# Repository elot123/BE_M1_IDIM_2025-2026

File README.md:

# BE_M1_IDIM_2025-2026

## Objectif du projet
Ce dépôt contient le travail réalisé dans le cadre du BE du M1 IDIM.
Il vise à modéliser et visualiser la trajectoire d’une particule à travers
différentes zones physiques.

## Description des fichiers

### `trajectoire.py`
Ce fichier contient les fonctions de calcul de la trajectoire :
- définition des paramètres géométriques des différentes zones
- calcul des positions et vitesses dans chaque zone
- fonction de tracé des trajectoires et des limites physiques

Il constitue le **cœur physique / mathématique** du projet.

### `interface_graphique.py`
Ce fichier implémente une interface graphique permettant :
- de modifier les paramètres physiques (énergie, tensions, activation des zones)
- de lancer le calcul de trajectoire
- d’afficher graphiquement les résultats

Il sert d’**interface utilisateur** entre le modèle et l’utilisateur.

## Utilisation

```bash
python interface_graphique.py

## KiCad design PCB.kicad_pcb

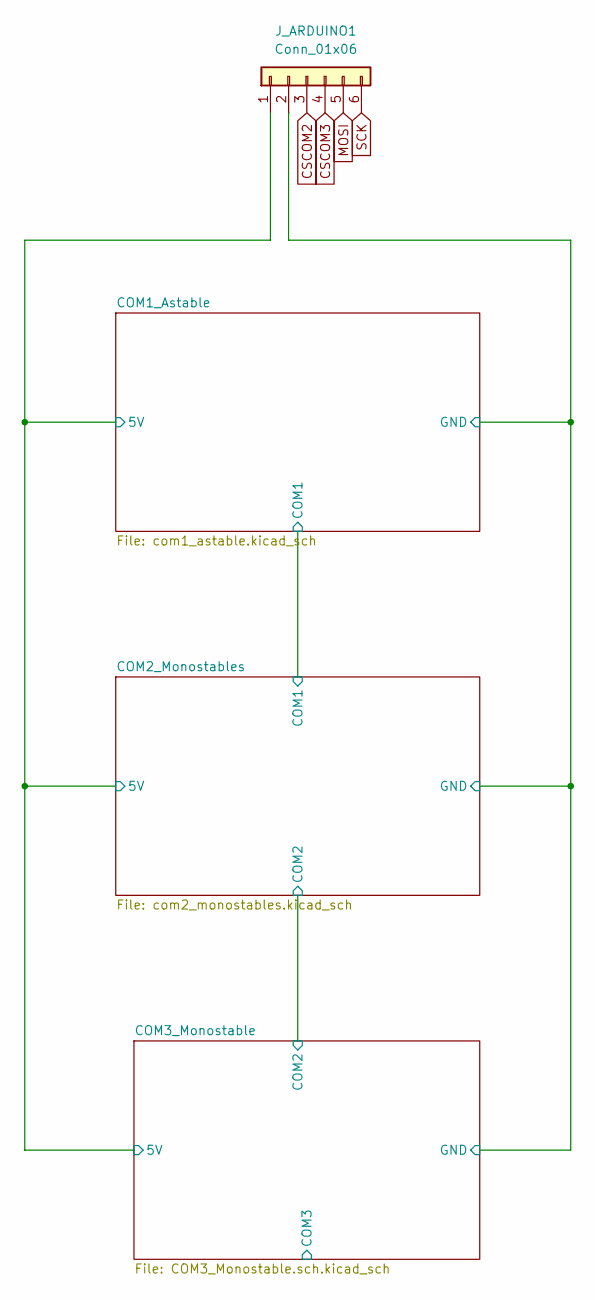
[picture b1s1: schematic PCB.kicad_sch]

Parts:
J_ARDUINO1: Conn_01x06; PinHeader_1x06_P2.54mm_Vertical

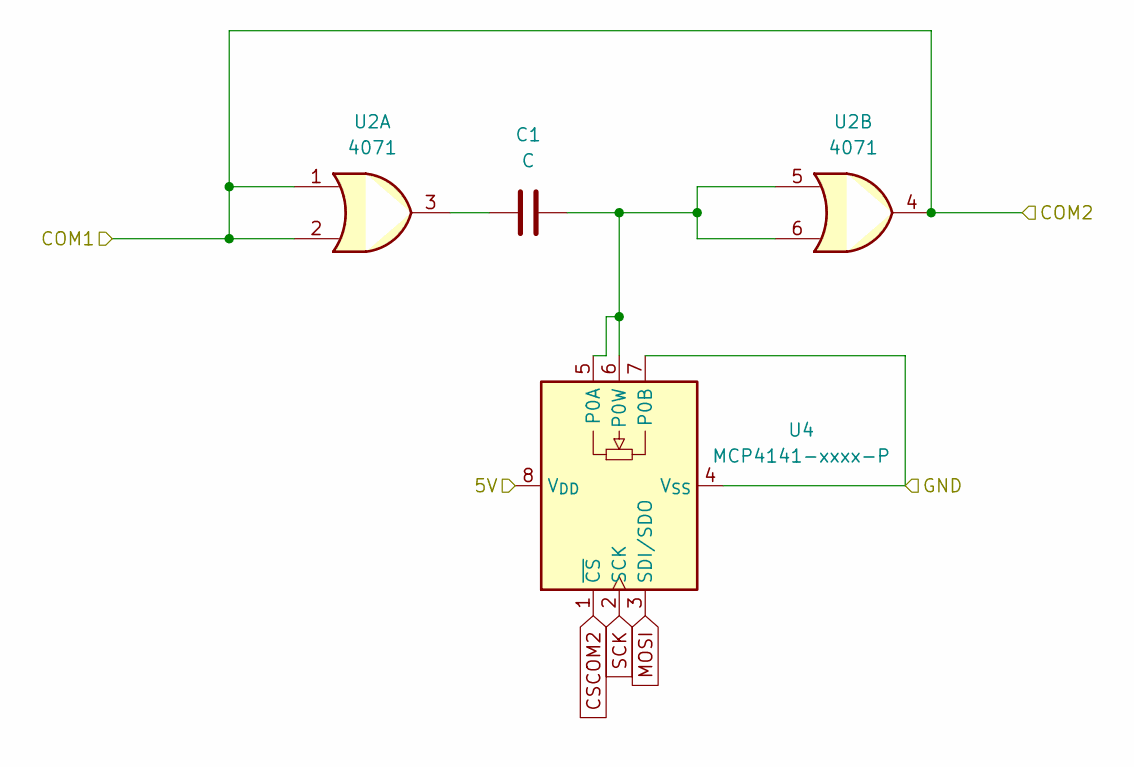
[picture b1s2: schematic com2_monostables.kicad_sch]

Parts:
C1: C; C_Disc_D5.0mm_W2.5mm_P5.00mm
U2: 4071; DIP-14_W7.62mm
U4: MCP4141-xxxx-P; DIP-8_W7.62mm

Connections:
/COM1_Astable/5V: U4.8 (V_{DD}); also elsewhere on the board
/COM1_Astable/COM1: U2.1, U2.2, U2.4; also elsewhere on the board
/COM1_Astable/GND: U4.4 (V_{SS}), U4.7 (P0B); also elsewhere on the board
CSCOM2: U4.1 (~CS)
MOSI: U4.3 (SDI/SDO); also elsewhere on the board
unnamed: C1.1, U2.3
unnamed: C1.2, U2.5, U2.6, U4.5 (P0A), U4.6 (P0W)
SCK: U4.2 (SCK); also elsewhere on the board

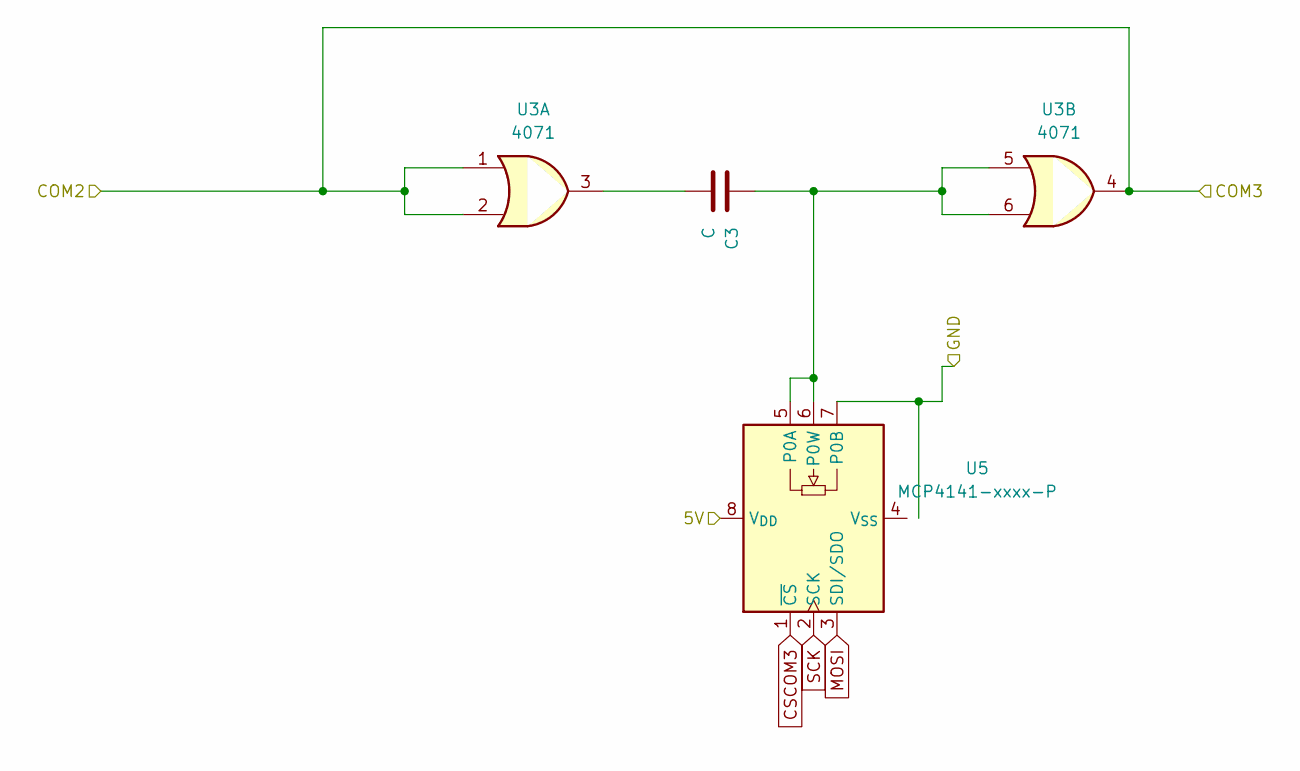
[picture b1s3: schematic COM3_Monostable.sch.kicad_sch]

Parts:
C3: C; C_Disc_D5.0mm_W2.5mm_P5.00mm
U3: 4071; DIP-14_W7.62mm
U5: MCP4141-xxxx-P; DIP-8_W7.62mm

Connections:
/COM1_Astable/5V: U5.8 (V_{DD}); also elsewhere on the board
/COM1_Astable/COM1: U3.1, U3.2, U3.4; also elsewhere on the board
/COM1_Astable/GND: U5.7 (P0B); also elsewhere on the board
CSCOM3: U5.1 (~CS)
MOSI: U5.3 (SDI/SDO); also elsewhere on the board
unnamed: C3.1, U3.3
unnamed: C3.2, U3.5, U3.6, U5.5 (P0A), U5.6 (P0W)
SCK: U5.2 (SCK); also elsewhere on the board

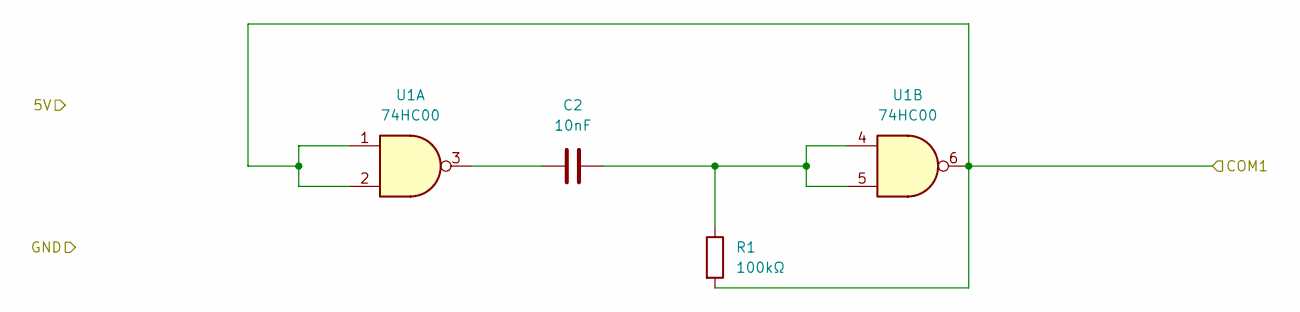
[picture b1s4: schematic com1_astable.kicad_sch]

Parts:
C2: 10nF; C_Disc_D5.0mm_W2.5mm_P5.00mm
R1: 100kΩ; R_Axial_DIN0207_L6.3mm_D2.5mm_P7.62mm_Horizontal
U1: 74HC00; DIP-14_W7.62mm

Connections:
/COM1_Astable/COM1: R1.2, U1.1, U1.2, U1.6; also elsewhere on the board
unnamed: C2.1, U1.3
unnamed: C2.2, R1.1, U1.4, U1.5

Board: 2 copper layers, 10 parts (0 on the bottom side), 11 nets, no tracks yet.

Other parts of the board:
ARDUINO_LEONARDO1: Conn_01x06; PinHeader_1x06_P2.54mm_Vertical

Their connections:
MOSI: ARDUINO_LEONARDO1.5; also elsewhere on the board
SCK: ARDUINO_LEONARDO1.6; also elsewhere on the board

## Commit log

2025-11-07 Première version trajectoire sans interface utilisateur
2025-11-07 Circuit monostable (COM2 et COM3) V1
2025-12-15 Ajout interface graphique + maj trajectoire
2025-12-15 Ajout explication des fichiers dans le README
2025-12-15 ajout pour KiCAD
2025-12-15 copie de trajectoire dans bad branche
2025-12-23 Dernière version des simulations circuits.
2026-03-02 Mise à jour de la simulation du multivibrateur stable
